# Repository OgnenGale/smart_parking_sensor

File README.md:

# IoT Smart Parking Sensor — PCB v1.0

Smart parking sensor for my university project.

2-layer board, **62 × 46 mm**, four M3 holes (3.2 mm, NPTH) 3.5 mm in from each corner.
Everything here is produced by `generate.py`, which writes all the files and then checks them:

```powershell
& "C:\Program Files\KiCad\10.0\bin\python.exe" generate.py
```

Results of the last run: **ERC 0 issues, DRC 0 issues (zones refilled, schematic parity checked)**. KiCad's own exported netlist matches the netlist below exactly.

## Read before you order

| # | Item | What I did / what you must check |
|---|------|----------------------------------|
| 1 | **SuperMini row spacing** | Measured with a ruler: 15.0 mm gap between pins + 0.66 mm pin width = **15.7 mm** centre to centre (`ROW_SPACING`). Pin pitch confirmed 2.54 mm (pin 1 to pin 5: 9.5 mm gap). Confirm on the 1:1 print before ordering. |
| 2 | SuperMini pin order | Confirmed from your photos: with USB-C at the bottom (top view), the left column top→bottom is `GPIO0 … GPIO4, 3V3, GND, 5V`. |
| 3 | **TP4056 (HW-373 V1.2.1) pads** | Order confirmed from your photos: `IN-`/`IN+` at the USB end (IN+ on the right), and `OUT-, B-, B+, OUT+` across the other end. Outer pads ±6.9 mm, B± at ±3.6 mm (`TP_PX`, `TP_BX`); IN row to OUT/B row **22.8 mm** (`TP_ROWS`). The first test print came out at 95.4% (59 × 44 mm), so these are corrected for that. **Print the template at 100% / Actual size and check the outline is 62 × 46 mm.** Fit it **USB-C toward J2** (marked on the silkscreen). |
| 4 | **SS-12D00G3 pitch** | Assumed 2.54 mm. Some clones use 2.0 mm, so check yours. |
| 5 | **Board size** | 50 × 40 mm doesn't fit the three modules, both keep-outs and four corner M3 holes without courtyard collisions, so the board is 62 × 46 mm. |
| 6 | ⚠ **USB while switched on** | The SuperMini `5V` pin is the USB VBUS line. With SW1 ON it connects through the protection MOSFETs straight to the battery, so a USB cable charges the LiPo directly with no current limit. **Turn SW1 OFF before connecting USB**; the silkscreen says so too. |
| 7 | **No boost converter** | The 5V pin gets raw battery voltage (3.0–4.2 V) into the onboard LDO. Below about 3.5 V, Wi‑Fi bursts may brown out. **C2 (100 µF)** at the 5V pin smooths the bursts; also check the battery in firmware before using Wi‑Fi (see below). |
| 7a | ⚠ **TP4056 charge current (rework)** | The HW-373 ships set to 1 A, which is 2.2C for a 450 mAh cell. **Replace its R_PROG** (the 1.2 kΩ resistor marked `122`, on TP4056 pin 2) with **3.0 kΩ**, which gives ~400 mA (0.9C). It's listed in the BOM as `U2 rework`. Solar alone gives only tens of mA, but USB-C charging on the module would use the full setting. |
| 8 | **JST-PH polarity** | It isn't standardized. J1 pin 1 = `+` (square pad). Your 752035 cell has bare leads, so crimp a PH plug with red to pin 1. Your solar panel's **blue** wire is `+`. |
| 9 | JST-XH pitch | Real XH pitch is 2.50 mm (the spec says 2.54); the stock KiCad footprint is used. |

## Netlist (also in `netlist.csv` / `netlist.json`)

| Net | Connections | Width |
|-----|-------------|-------|
| SOLAR_P | J2.1 (+) — U2 IN+ | 0.6 mm |
| SOLAR_N | J2.2 (−) — U2 IN− | 0.6 mm |
| BAT_P | J1.1 (+) — U2 B+ | 0.6 mm |
| BAT_N | J1.2 (−) — U2 B− | 0.6 mm |
| VOUT | U2 OUT+ — SW1.1 | 0.6 mm |
| VSYS | SW1.2 (common) — U1 5V — R1.1 — C2.1 | 0.6 mm |
| +3V3 | U1 3V3 — U3 VCC | 0.6 mm |
| GND | U2 OUT−, U1 GND, U3 GND, R2.2, C1.2, C2.2, D1 K | bottom pour |
| SDA | U1 GPIO8 — U3 SDA | 0.25 mm |
| SCL | U1 GPIO9 — U3 SCL | 0.25 mm |
| VBAT_SENSE | R1.2 — R2.1 — C1.1 — U1 GPIO0 (ADC1_CH0) | 0.25 mm |
| LED_DRV | U1 GPIO1 — R3.1 | 0.25 mm |
| LED_A | R3.2 — D1 A | 0.25 mm |
| *no connect* | U3 DRDY, SW1.3, U1 GPIO2–7/10/20/21 | — |

## Wiring diagram

```
 SOLAR 5-6V            TP4056 + DW01A/FS8205A (U2)
 J2 (+) ───SOLAR_P───► IN+                    OUT+ ──VOUT──► SW1.1 ┐
 J2 (-) ───SOLAR_N───► IN-                    OUT- ──GND          │ SW1 (SS-12D00G3)
                                                                   │
 LIPO 3.7V 450mAh                                     SW1.2 (COM) ◄┘
 J1 (+) ───BAT_P─────► B+                               │ VSYS (switched)
 J1 (-) ───BAT_N─────► B-                               ├──────────────► U1 5V  (onboard LDO)
                                                        │
                                                       R1 100k 1%
                                                        │
                       U1 GPIO0 (ADC1_CH0) ◄────────────┼── VBAT_SENSE  (4.2 V → 2.1 V)
                                                        │
                                                R2 100k ┴ ┬ C1 100nF
                                                        GND
 ESP32-C3 SuperMini (U1)            GY-271 (U3)
   3V3   ────── +3V3 ──────────────► VCC
   GND   ────── GND ───────────────► GND
   GPIO9 ────── SCL ───────────────► SCL
   GPIO8 ────── SDA ───────────────► SDA
                                     DRDY  ✕ (no connect)

   GPIO1 ── LED_DRV ── R3 220R ── LED_A ──► D1 anode   D1 cathode ── GND
```

## Board layout (top view, USB-C at the bottom edge)

```
 0                                                           62 mm
 ┌──────────────────────────────────────────────────────────────┐ 0
 │ (H1)   [J2 SOLAR]       PARKING SENSOR v1.0            (H2)   │
 │ ┌─────────────┐                                ┌──────────┐ │
 │ │IN-       IN+│  ┌─── +3V3 trace (y=12) ───┐    │  GY-271  │ │
 │ │             │  │                         │    │   (U3)   │ │
 │ │   TP4056    │  │  ░░ ANTENNA KEEP-OUT ░░ │    │▓ MAG     │ │
 │ │    (U2)     │  │  ░░  no copper, both ░░ │    │▓ KEEP-OUT│ │
 │ │             │  │  ░░  layers           ░░└───►VCC GND SCL SDA DRDY
 │ │             │  │ ┌─┐  ESP32-C3     ┌─┐         ▲   ▲      │
 │ │             │  │ │0│  SuperMini    │ │  SCL ───┘   │      │
 │ │             │  │ │ │  (U1, socket) │ │  SDA ───────┘      │
 │ │OUT- B- B+ OUT+ │ │ │ R1 R2 C1      │ │                    │
 │ └─────────────┘  └─│ │ (under module)│ │                    │
 │  [J1 BATT] [SW1 PWR] │5V   USB-C     └─┘  R3  D1            │
 │ (H3)                 └──────────────┘                (H4)   │
 └──────────────────────────────────────────────────────────────┘ 46
```

The rendered board is in `diagrams/render_top.png` and `render_bottom.png`, the per-layer copper in `pcb_top.svg` and `pcb_bottom.svg`, and the schematic in `diagrams/parking_sensor.svg` and `schematic.pdf`.

## Layout rules as implemented

1. **Magnetometer keep-out**: a rule area on both copper layers under the GY-271 body (x 45–58, y 7.75–20 mm) blocks tracks, vias and pour. Every GY-271 trace comes in from below the header. The battery and charge paths (`BAT±`, `VOUT`, `VSYS`) all stay on the left half, more than 23 mm from the sensor chip. The only trace nearby is `+3V3`, which carries about 1 mA to the sensor.
2. **Antenna keep-out**: a rule area on both layers from the SuperMini's antenna end out to 7.5 mm beyond it (x 24–42, y 16–24.6). It's printed on silkscreen as "ANTENNA KEEP-OUT / NO COPPER".
3. **Track widths**: power nets are 0.6 mm and signals 0.25 mm. Both minimums are enforced by DRC rules in `parking_sensor.kicad_dru`.
4. **GND**: one solid bottom pour (0.3 mm clearance, thermal reliefs) with cut-outs only for the keep-outs. Only one track runs on the bottom layer: a 9.6 mm `LED_DRV` jumper under the ESP32, which lets it cross `VBAT_SENSE`.
5. **Parts under the module**: the SuperMini sits about 8.5 mm up on its female headers, so R1, R2, C1 (0805) and C2 (1210) fit underneath it. The module's courtyard covers only the two header rows.

## Files

| File | What it is |
|------|-----------|
| `parking_sensor.kicad_pro/.kicad_sch/.kicad_pcb` | KiCad 10 project. Open the `.kicad_pro`. EasyEDA Pro can import these via *File → Import → KiCad*. |
| `parking_sensor.pretty/` | Footprints for the SuperMini, TP4056, GY-271 and SS-12D00G3 |
| `parking_sensor.kicad_sym` | Matching schematic symbols |
| `parking_sensor.kicad_dru` | Custom DRC rules (track widths) |
| `bom.csv`, `bom.json` | Bill of materials |
| `netlist.csv`, `netlist.json` | Netlist, one row per pin. `kicad_netlist.xml` is KiCad's own export of it. |
| `gerbers/` | Gerbers, drill file, top placement file. Zip this folder to order boards. |
| `diagrams/` | Schematic SVG/PDF, PCB layer SVGs, 3D renders |
| `erc.json`, `drc.json` | Reports from the last check run |
| `generate.py` | The single source of truth. Edit it and re-run instead of hand-editing the board if you want to keep the checks. |

## Firmware notes

- ADC: use `analogReadMilliVolts(0) * 2` with 11 dB attenuation. 4.2 V reads as 2.1 V, inside the ~2.5 V range. The divider is 100k/100k (~21 µA drain); C1 keeps readings stable, but sample slowly (one reading, or a few ms apart).
- Low battery: read the battery **before** starting Wi‑Fi. Under 3.5 V, skip Wi‑Fi and deep-sleep (e.g. 30 min) until solar recovers it. Lower the transmit power (`WiFi.setTxPower(WIFI_POWER_8_5dBm)`) if the link allows.
- If your SuperMini has an always-on power LED, removing it saves a few mA (days of battery).
- I2C: `Wire.begin(8, 9)` (SDA, SCL). QMC5883L is at 0x0D and HMC5883L at 0x1E, so check which chip your GY-271 has.
- GPIO8 also drives the SuperMini's onboard LED, so it flickers during I2C traffic. That's harmless.
- When charging from solar, the TP4056 current changes the field near the board slightly. Calibrate the empty-spot baseline in firmware rather than relying on one absolute value.

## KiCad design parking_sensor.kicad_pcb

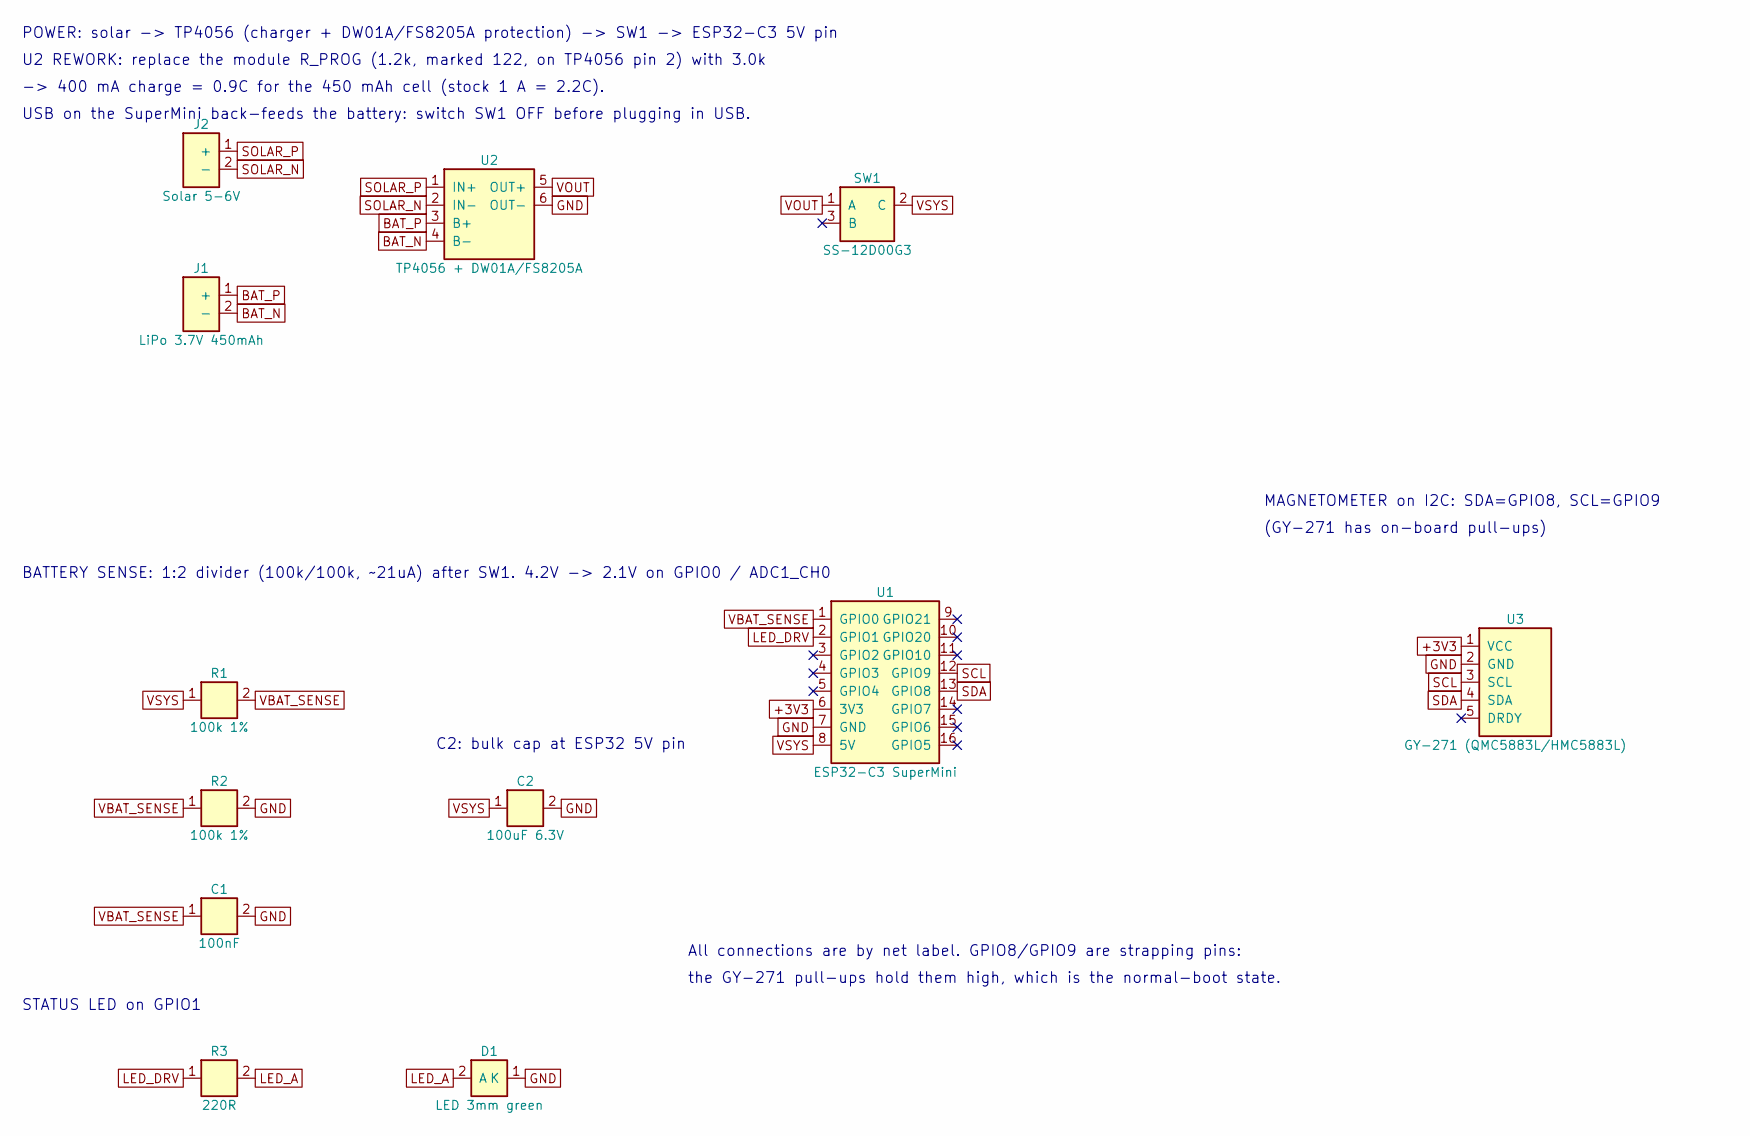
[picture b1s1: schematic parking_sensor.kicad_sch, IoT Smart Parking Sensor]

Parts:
C1: 100nF; C_0805_2012Metric
C2: 100uF 6.3V; C_1210_3225Metric
D1: LED 3mm green; LED_D3.0mm
J1: LiPo 3.7V 450mAh; JST_PH_S2B-PH-K_1x02_P2.00mm_Horizontal
J2: Solar 5-6V; JST_XH_B2B-XH-A_1x02_P2.50mm_Vertical
R1, R2: 100k 1%; R_0805_2012Metric
R3: 220R; R_0805_2012Metric
SW1: SS-12D00G3; SW_Slide_SPDT_SS-12D00G3
U1: ESP32-C3 SuperMini; ESP32-C3_SuperMini_Socketed
U2: TP4056 + DW01A/FS8205A; TP4056_Module_Protected
U3: GY-271 (QMC5883L/HMC5883L); GY-271_Module

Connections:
+3V3: U1.6 (3V3), U3.1 (VCC)
BAT_N: J1.2 (-), U2.4 (B-)
BAT_P: J1.1 (+), U2.3 (B+)
GND: C1.2, C2.2, D1.1 (K), R2.2, U1.7 (GND), U2.6 (OUT-), U3.2 (GND)
LED_A: D1.2 (A), R3.2
LED_DRV: R3.1, U1.2 (GPIO1)
SCL: U1.12 (GPIO9), U3.3 (SCL)
SDA: U1.13 (GPIO8), U3.4 (SDA)
SOLAR_N: J2.2 (-), U2.2 (IN-)
SOLAR_P: J2.1 (+), U2.1 (IN+)
VBAT_SENSE: C1.1, R1.2, R2.1, U1.1 (GPIO0)
VOUT: SW1.1 (A), U2.5 (OUT+)
VSYS: C2.1, R1.1, SW1.2 (C), U1.8 (5V)

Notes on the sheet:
POWER: solar -> TP4056 (charger + DW01A/FS8205A protection) -> SW1 -> ESP32-C3 5V pin
BATTERY SENSE: 1:2 divider (100k/100k, ~21uA) after SW1. 4.2V -> 2.1V on GPIO0 / ADC1_CH0
STATUS LED on GPIO1
U2 REWORK: replace the module R_PROG (1.2k, marked 122, on TP4056 pin 2) with 3.0k
-> 400 mA charge = 0.9C for the 450 mAh cell (stock 1 A = 2.2C).
USB on the SuperMini back-feeds the battery: switch SW1 OFF before plugging in USB.
C2: bulk cap at ESP32 5V pin
MAGNETOMETER on I2C: SDA=GPIO8, SCL=GPIO9
(GY-271 has on-board pull-ups)
All connections are by net label. GPIO8/GPIO9 are strapping pins:
the GY-271 pull-ups hold them high, which is the normal-boot state.

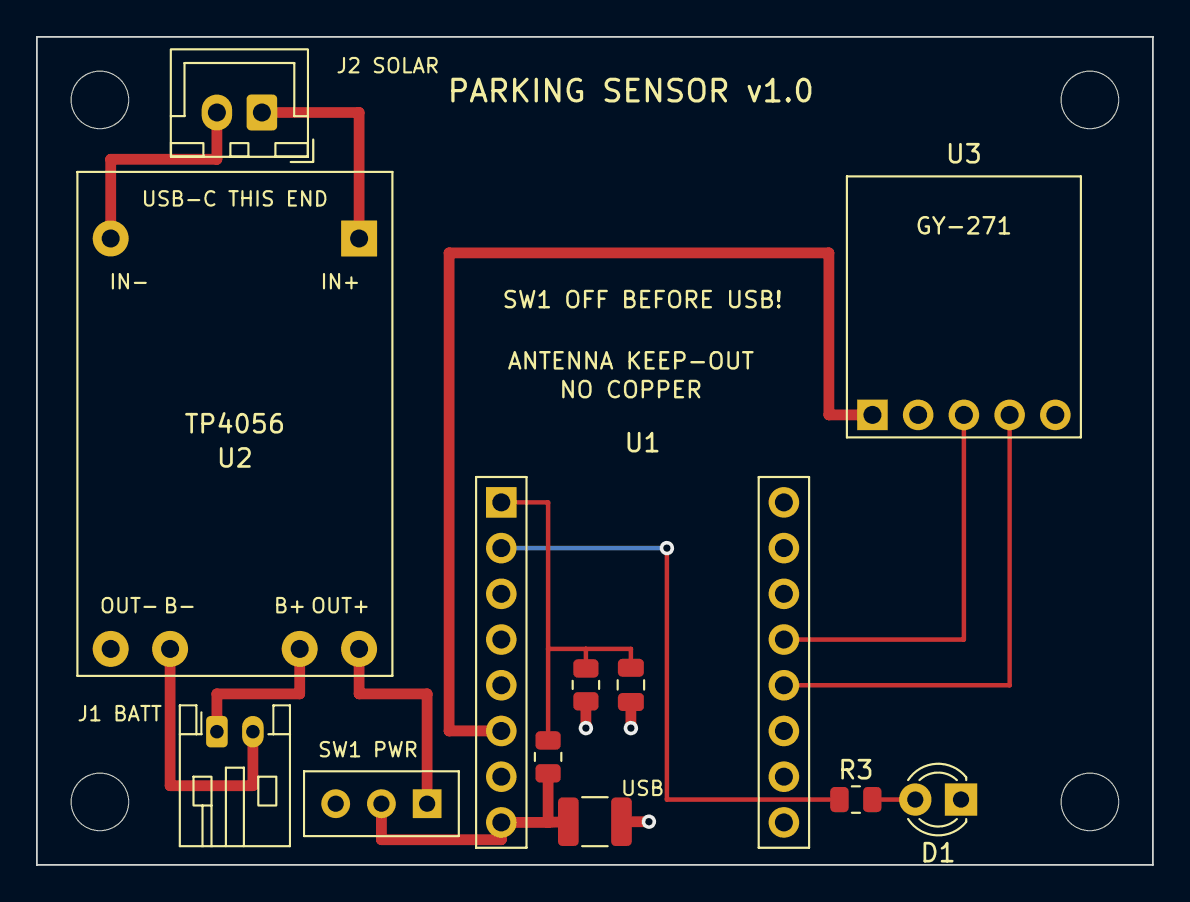
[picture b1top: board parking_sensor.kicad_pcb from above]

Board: 2 copper layers, 62.0 x 46.0 mm, 16 parts (0 on the bottom side), 13 nets.

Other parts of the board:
H1, H2, H3, H4: M3; MountingHole_3.2mm_M3

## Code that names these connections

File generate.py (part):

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         fp="parking_sensor:ESP32-C3_SuperMini_Socketed",
         desc="ESP32-C3 SuperMini dev board on 2x 1x8 2.54mm female headers",
         bom="ESP32-C3 SuperMini + 2x 1x8 female header 2.54mm",
         pins=[("1", "GPIO0", "VBAT_SENSE", "L"), ("2", "GPIO1", "LED_DRV", "L"),
               ("3", "GPIO2", None, "L"), ("4", "GPIO3", None, "L"),
               ("5", "GPIO4", None, "L"), ("6", "3V3", "+3V3", "L"),
               ("7", "GND", "GND", "L"), ("8", "5V", "VSYS", "L"),
               ("9", "GPIO21", None, "R"), ("10", "GPIO20", None, "R"),
               ("11", "GPIO10", None, "R"), ("12", "GPIO9", "SCL", "R"),
               ("13", "GPIO8", "SDA", "R"), ("14", "GPIO7", None, "R"),
               ("15", "GPIO6", None, "R"), ("16", "GPIO5", None, "R")],
         sch=(147.32, 116.84), pcb=(U1_X, 34.75, 0)),
    dict(ref="U2", value="TP4056 + DW01A/FS8205A", sym="TP4056_Module", w=12.7,
         fp="parking_sensor:TP4056_Module_Protected",
         desc="TP4056 1S Li-ion charger module with DW01A + FS8205A protection",
         bom="TP4056 charger module with protection (USB-C or micro-USB)",
         pins=[("1", "IN+", "SOLAR_P", "L"), ("2", "IN-", "SOLAR_N", "L"),
               ("3", "B+", "BAT_P", "L"), ("4", "B-", "BAT_N", "L"),
               ("5", "OUT+", "VOUT", "R"), ("6", "OUT-", "GND", "R")],
         sch=(91.44, 50.8), pcb=(11.0, 21.5, 0)),
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         fp="Connector_JST:JST_PH_S2B-PH-K_1x02_P2.00mm_Horizontal",
         desc="Battery connector, JST-PH 2.0mm right-angle",
         bom="JST PH S2B-PH-K-S right-angle 2-pin",
         pins=[("1", "+", "BAT_P", "R"), ("2", "-", "BAT_N", "R")],
         sch=(50.8, 63.5), pcb=(10.0, 38.6, 0)),
    dict(ref="J2", value="Solar 5-6V", sym="Conn_Pwr_2", w=5.08,
         fp="Connector_JST:JST_XH_B2B-XH-A_1x02_P2.50mm_Vertical",
         desc="Solar panel input, JST-XH 2.5mm vertical",
         bom="JST XH B2B-XH-A vertical 2-pin",
         pins=[("1", "+", "SOLAR_P", "R"), ("2", "-", "SOLAR_N", "R")],
         sch=(50.8, 43.18), pcb=(12.5, 4.2, 180)),
    dict(ref="SW1", value="SS-12D00G3", sym="SW_SPDT", w=7.62,
         fp="parking_sensor:SW_Slide_SPDT_SS-12D00G3",
         desc="SPDT slide switch, power disconnect",
         bom="SS-12D00G3 SPDT slide switch",
         pins=[("1", "A", "VOUT", "L"), ("3", "B", None, "L"), ("2", "C", "VSYS", "R")],
         sch=(144.78, 50.8), pcb=(19.14, 42.6, 180)),
    dict(ref="R1", value="100k 1%", sym="R", w=5.08,
         fp="Resistor_SMD:R_0805_2012Metric",
         desc="Battery divider top (100k: ~21uA drain)", bom="100k 1% 0805",
         pins=[("1", "~", "VSYS", "L"), ("2", "~", "VBAT_SENSE", "R")],
         sch=(53.34, 119.38), pcb=(28.4, 40.0, 90)),
    dict(ref="R2", value="100k 1%", sym="R", w=5.08,
         fp="Resistor_SMD:R_0805_2012Metric",
         desc="Battery divider bottom (100k: ~21uA drain)", bom="100k 1% 0805",
         pins=[("1", "~", "VBAT_SENSE", "L"), ("2", "~", "GND", "R")],
         sch=(53.34, 134.62), pcb=(30.5, 36.0, 90)),
    dict(ref="C1", value="100nF", sym="C", w=5.08,
         fp="Capacitor_SMD:C_0805_2012Metric",
         desc="ADC filter", bom="100nF X7R 0805 ceramic",
         pins=[("1", "~", "VBAT_SENSE", "L"), ("2", "~", "GND", "R")],
         sch=(53.34, 149.86), pcb=(33.0, 36.0, 90)),
    dict(ref="C2", value="100uF 6.3V", sym="C", w=5.08,
         fp="Capacitor_SMD:C_1210_3225Metric",
         desc="Bulk cap at ESP32 5V pin, rides through Wi-Fi bursts",
         bom="100uF 6.3V X5R 1210 ceramic (e.g. Murata GRM32ER60J107)",
         pins=[("1", "~", "VSYS", "L"), ("2", "~", "GND", "R")],
         sch=(96.52, 134.62), pcb=(31.0, 43.6, 0)),
    dict(ref="R3", value="220R", sym="R", w=5.08,
         fp="Resistor_SMD:R_0805_2012Metric",
         desc="LED current limit", bom="220R 0805",
         pins=[("1", "~", "LED_DRV", "L"), ("2", "~", "LED_A", "R")],
         sch=(53.34, 172.72), pcb=(45.5, 42.37, 0)),
    dict(ref="D1", value="LED 3mm green", sym="LED", w=5.08,
         fp="LED_THT:LED_D3.0mm",
         desc="Status LED", bom="3mm LED green/blue",
         pins=[("2", "A", "LED_A", "L"), ("1", "K", "GND", "R")],
         sch=(91.44, 172.72), pcb=(51.34, 42.37, 180)),
]
HOLES = [(3.5, 3.5), (BOARD_W - 3.5, 3.5), (3.5, BOARD_H - 3.5), (BOARD_W - 3.5, BOARD_H - 3.5)]
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
    notes = [
        (25.4, 25.4, "POWER: solar -> TP4056 (charger + DW01A/FS8205A protection) -> SW1 -> ESP32-C3 5V pin"),
        (25.4, 101.6, "BATTERY SENSE: 1:2 divider (100k/100k, ~21uA) after SW1. 4.2V -> 2.1V on GPIO0 / ADC1_CH0"),
        (25.4, 162.56, "STATUS LED on GPIO1"),
        (25.4, 29.21, "U2 REWORK: replace the module R_PROG (1.2k, marked 122, on TP4056 pin 2) with 3.0k"),
        (25.4, 33.02, "-> 400 mA charge = 0.9C for the 450 mAh cell (stock 1 A = 2.2C)."),
        (25.4, 36.83, "USB on the SuperMini back-feeds the battery: switch SW1 OFF before plugging in USB."),
        (83.82, 125.73, "C2: bulk cap at ESP32 5V pin"),
        (200.66, 91.44, "MAGNETOMETER on I2C: SDA=GPIO8, SCL=GPIO9"),
        (200.66, 95.25, "(GY-271 has on-board pull-ups)"),
        (119.38, 154.94, "All connections are by net label. GPIO8/GPIO9 are strapping pins:"),
        (119.38, 158.75, "the GY-271 pull-ups hold them high, which is the normal-boot state."),
    ]
    for x, y, t in notes:
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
